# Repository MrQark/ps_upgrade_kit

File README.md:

# Power Supply Upgrade Kit

Power Supply Upgrade Kit (PSUK) allows to turn a power supply into LiFePO4 charger

# Objectives

To convert the existing power supply [ATABA S-360-12](https://prom.ua/ua/p1276775685-impulsnyj-blok-pitaniya.html) into LiFePO4 battery charger.

# Requirements

1. Current regulation.

REQ-001. PSUK shall linearly regulate output current up to the Threshold Value.

REQ-002. Current regulation Threshold Value selection shall be done by the variable resistor in the range from 5A to 25A (wider range is also acceptable).

REQ-003. Switching to current regulation shall be indicated by the yellow LED.

REQ-004. Current regulation shall not decrease output voltage lower than 10V to preserve the Fan operation in the current regulation mode.

2. Battery isolation.

REQ-005. If no AC power available the PSUK output shall be electically disconnected from the battery to avoid battery disharge by the fan and voltage feedback stages.

3. Voltage regulation.

REQ-006. PSUK shall extend the output voltage adjustment range up to 15V. Note: in the original state it is limited to 14-14.1V.

4. Fan control.

REQ-007. PSUK shall not activate the cooling FAN if the output current is near zero (0-0.3A) otherwise the FAN shall be operating.

Note: this requirement is for supporting the UPS use case when the soundless operation is preferred.

# Concept

# Power Supply data

# References

https://danyk.cz/reverz44_en.html

https://elektrotanya.com/s-360-12_12v_30a_power_supply_sch.pdf/download.html

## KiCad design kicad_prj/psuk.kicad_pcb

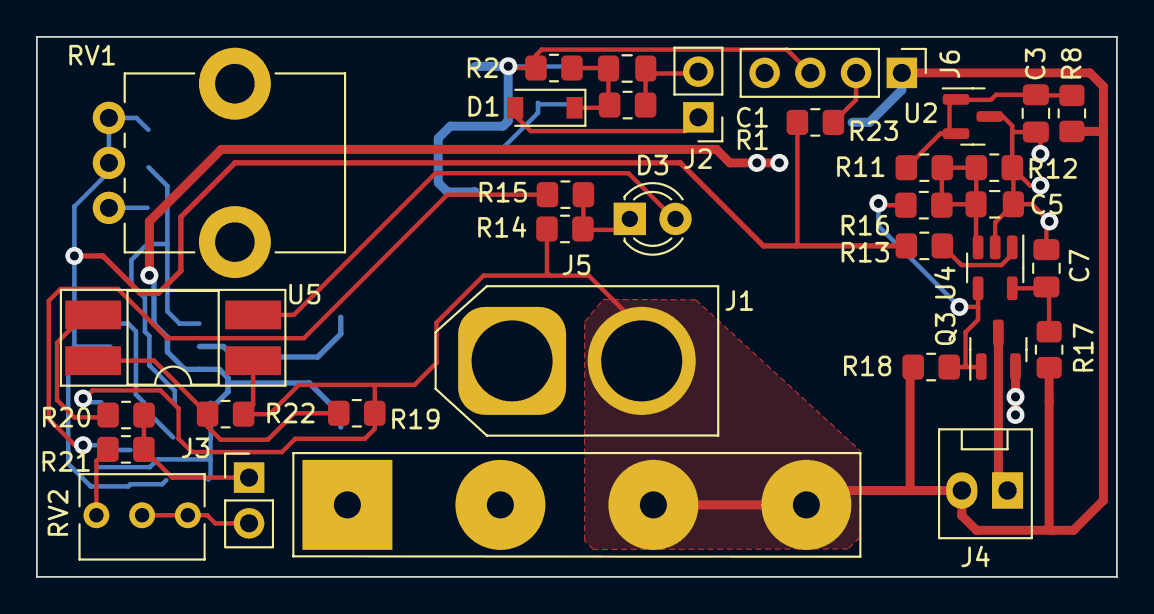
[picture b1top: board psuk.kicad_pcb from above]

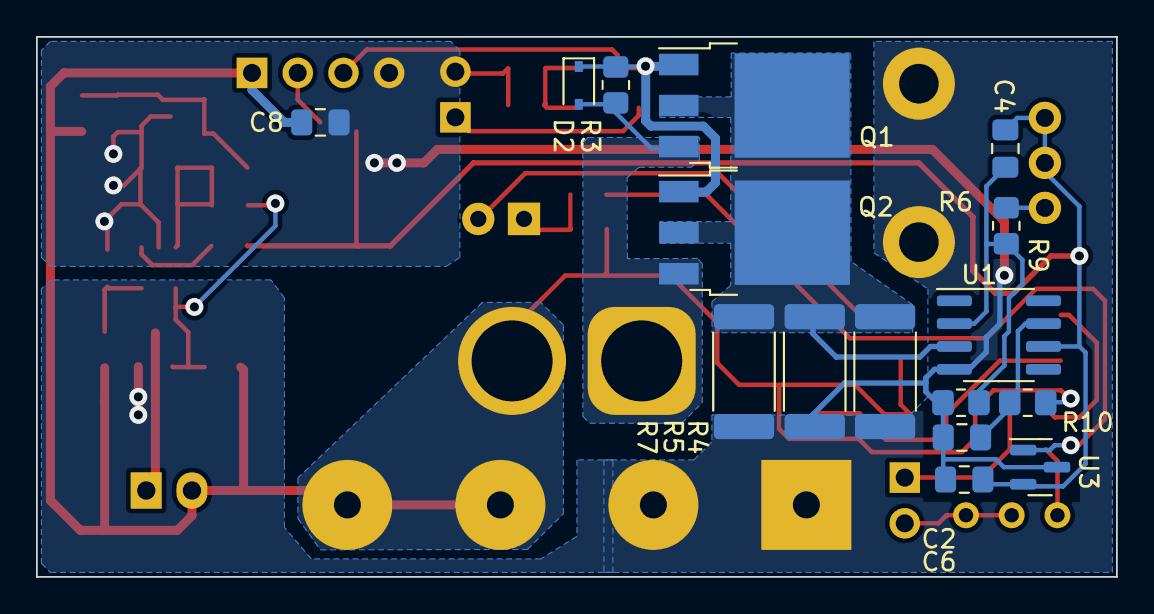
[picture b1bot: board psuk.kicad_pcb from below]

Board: 2 copper layers, 60.0 x 30.0 mm, 50 parts (16 on the bottom side), 26 nets.

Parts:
C1: 10u/25V; C_0805_2012Metric_Pad1.18x1.45mm_HandSolder
C2, C3, C5, C7, C8: 100n; C_0805_2012Metric_Pad1.18x1.45mm_HandSolder
C4: 150pF; C_0805_2012Metric_Pad1.18x1.45mm_HandSolder
C6: 1n; C_0805_2012Metric_Pad1.18x1.45mm_HandSolder
D1: 1N4148W; D_SOD-123
D2: BZX384B10; D_SOD-323
D3: YEL-3mm; LED_D3.0mm
J1: ATABA S-360-12 connector
J2, J3: 22-23-2021; PinHeader_1x02_P2.54mm_Vertical
J4: XH2.54-2P; FanPinHeader_1x02_P2.54mm_Vertical
J5: XT-60F; AMASS_XT60-F_1x02_P7.20mm_Vertical
J6: Conn_01x04_Male; PinHeader_1x04_P2.54mm_Vertical
Q1, Q2: AOD240; TO-252-3_TabPin2
Q3: IRLML2502TRPBF; SOT-23
R1, R3, R18: 15k; R_0805_2012Metric_Pad1.20x1.40mm_HandSolder
R2, R8, R12, R15: 2k2; R_0805_2012Metric_Pad1.20x1.40mm_HandSolder
R4, R5, R7: R003; R_2512_6332Metric_Pad1.40x3.35mm_HandSolder
R6, R10, R13, R17, R23: 47; R_0805_2012Metric_Pad1.20x1.40mm_HandSolder
R9: 4k3; R_0805_2012Metric_Pad1.20x1.40mm_HandSolder
R11, R19, R20: 30k; R_0805_2012Metric_Pad1.20x1.40mm_HandSolder
R14: 1k; R_0805_2012Metric_Pad1.20x1.40mm_HandSolder
R16: 1M; R_0805_2012Metric_Pad1.20x1.40mm_HandSolder
R21: 3k; R_0805_2012Metric_Pad1.20x1.40mm_HandSolder
R22: DNM; R_0805_2012Metric_Pad1.20x1.40mm_HandSolder
RV1: 10k; Potentiometer_Bourns_PTV09A-1_Single_Vertical
RV2: 1k; Potentiometer_Bourns_3266Y_Vertical
U1: OPA189IDR; SOIC-8_3.9x4.9mm_P1.27mm
U2, U3: TL431DBZ; SOT-23
U4: LM397; SOT-23-5
U5: FOD817B3SD; DIP-4_W8.89mm_SMDSocket_LongPads

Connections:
+12V: C8.2, J1.3 (+), J1.4 (+), J4.2, J5.2, J6.1, R8.1, R10.2, R14.1, R17.2, R18.2, R19.1, R22.1, U5.1
GND: C1.1, C2.1, C3.1, C5.1, C6.1, C7.1, C8.1, J1.1 (-), J1.2 (-), J2.2, J6.4, Q3.2 (S), R1.2, R4.2, R5.2, R6.1, R7.2, R12.2, RV1.MP (MountPin), U1.4 (V-), U2.3 (A), U3.3 (A), U4.2 (V-)
unnamed: C1.2, D1.1 (K), R1.1, R2.1
unnamed: C2.2, R10.1, U1.7 (V+)
unnamed: C3.2, R8.2, R11.1, U2.1 (K), U2.2 (REF)
unnamed: C4.1, C6.2, R13.1, R23.1, RV1.2, RV1.3, U1.6, U3.2 (REF)
unnamed: C4.2, R6.2, R9.1, U1.2 (-)
unnamed: C5.2, R11.2, R12.1, R16.1, U4.3 (+)
unnamed: C7.2, R17.1, U4.5 (V+)
unnamed: D1.2 (A), J2.1
unnamed: D2.1 (K), J6.3, Q1.1 (G), Q2.1 (G), R2.2, R3.1
unnamed: D2.2 (A), J5.1, Q1.3 (S), Q2.3 (S), R3.2
unnamed: D3.1 (K), R14.2, R15.1
unnamed: D3.2 (A), U5.2
unnamed: J3.1, R20.2, R21.1
unnamed: J3.2, RV2.1, RV2.2
unnamed: J4.1, Q3.3 (D)
unnamed: J6.2, R23.2
unnamed: Q1.2 (D), Q2.2 (D), R4.1, R5.1, R7.1, U1.3 (+)
unnamed: Q3.1 (G), R16.2, R18.1, U4.4
unnamed: R9.2, RV1.1
unnamed: R13.2, U4.1 (-)
unnamed: R15.2, U3.1 (K)
unnamed: R19.2, R22.2, U5.4
unnamed: R20.1, U5.3
unnamed: R21.2, RV2.3

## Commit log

2023-02-03 Renamed PS image.
2023-02-03 Updated the PSUK schematics.
2023-02-04 Updated schematics. Fixed wrong and missing 3D models.
2023-02-04 Added unsaved changes in schematics.
2023-02-06 Completed PCB routing. Released v1.0 artifact for production and procurement purposes.
